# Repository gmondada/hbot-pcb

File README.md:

# HBOT - PCB

This is the KiCad projet for a 24-RC-servo controller. It has been designed to control the [HBOT Humanoid Robot](https://github.com/gmondada/hbot-main). It is based on a STM32F4 (Cortex M4) microcontroller and has a socket to hold a WEMOS D1 mini.

# The HBOT in action

See [Full Demo on YouTube](https://youtu.be/EHFqUxe0FO4).

# License

Copyright (c) 2019 Gabriele Mondada.
Licensed under the [Creative Commons CC-BY 4.0 License](https://creativecommons.org/licenses/by/4.0/legalcode).

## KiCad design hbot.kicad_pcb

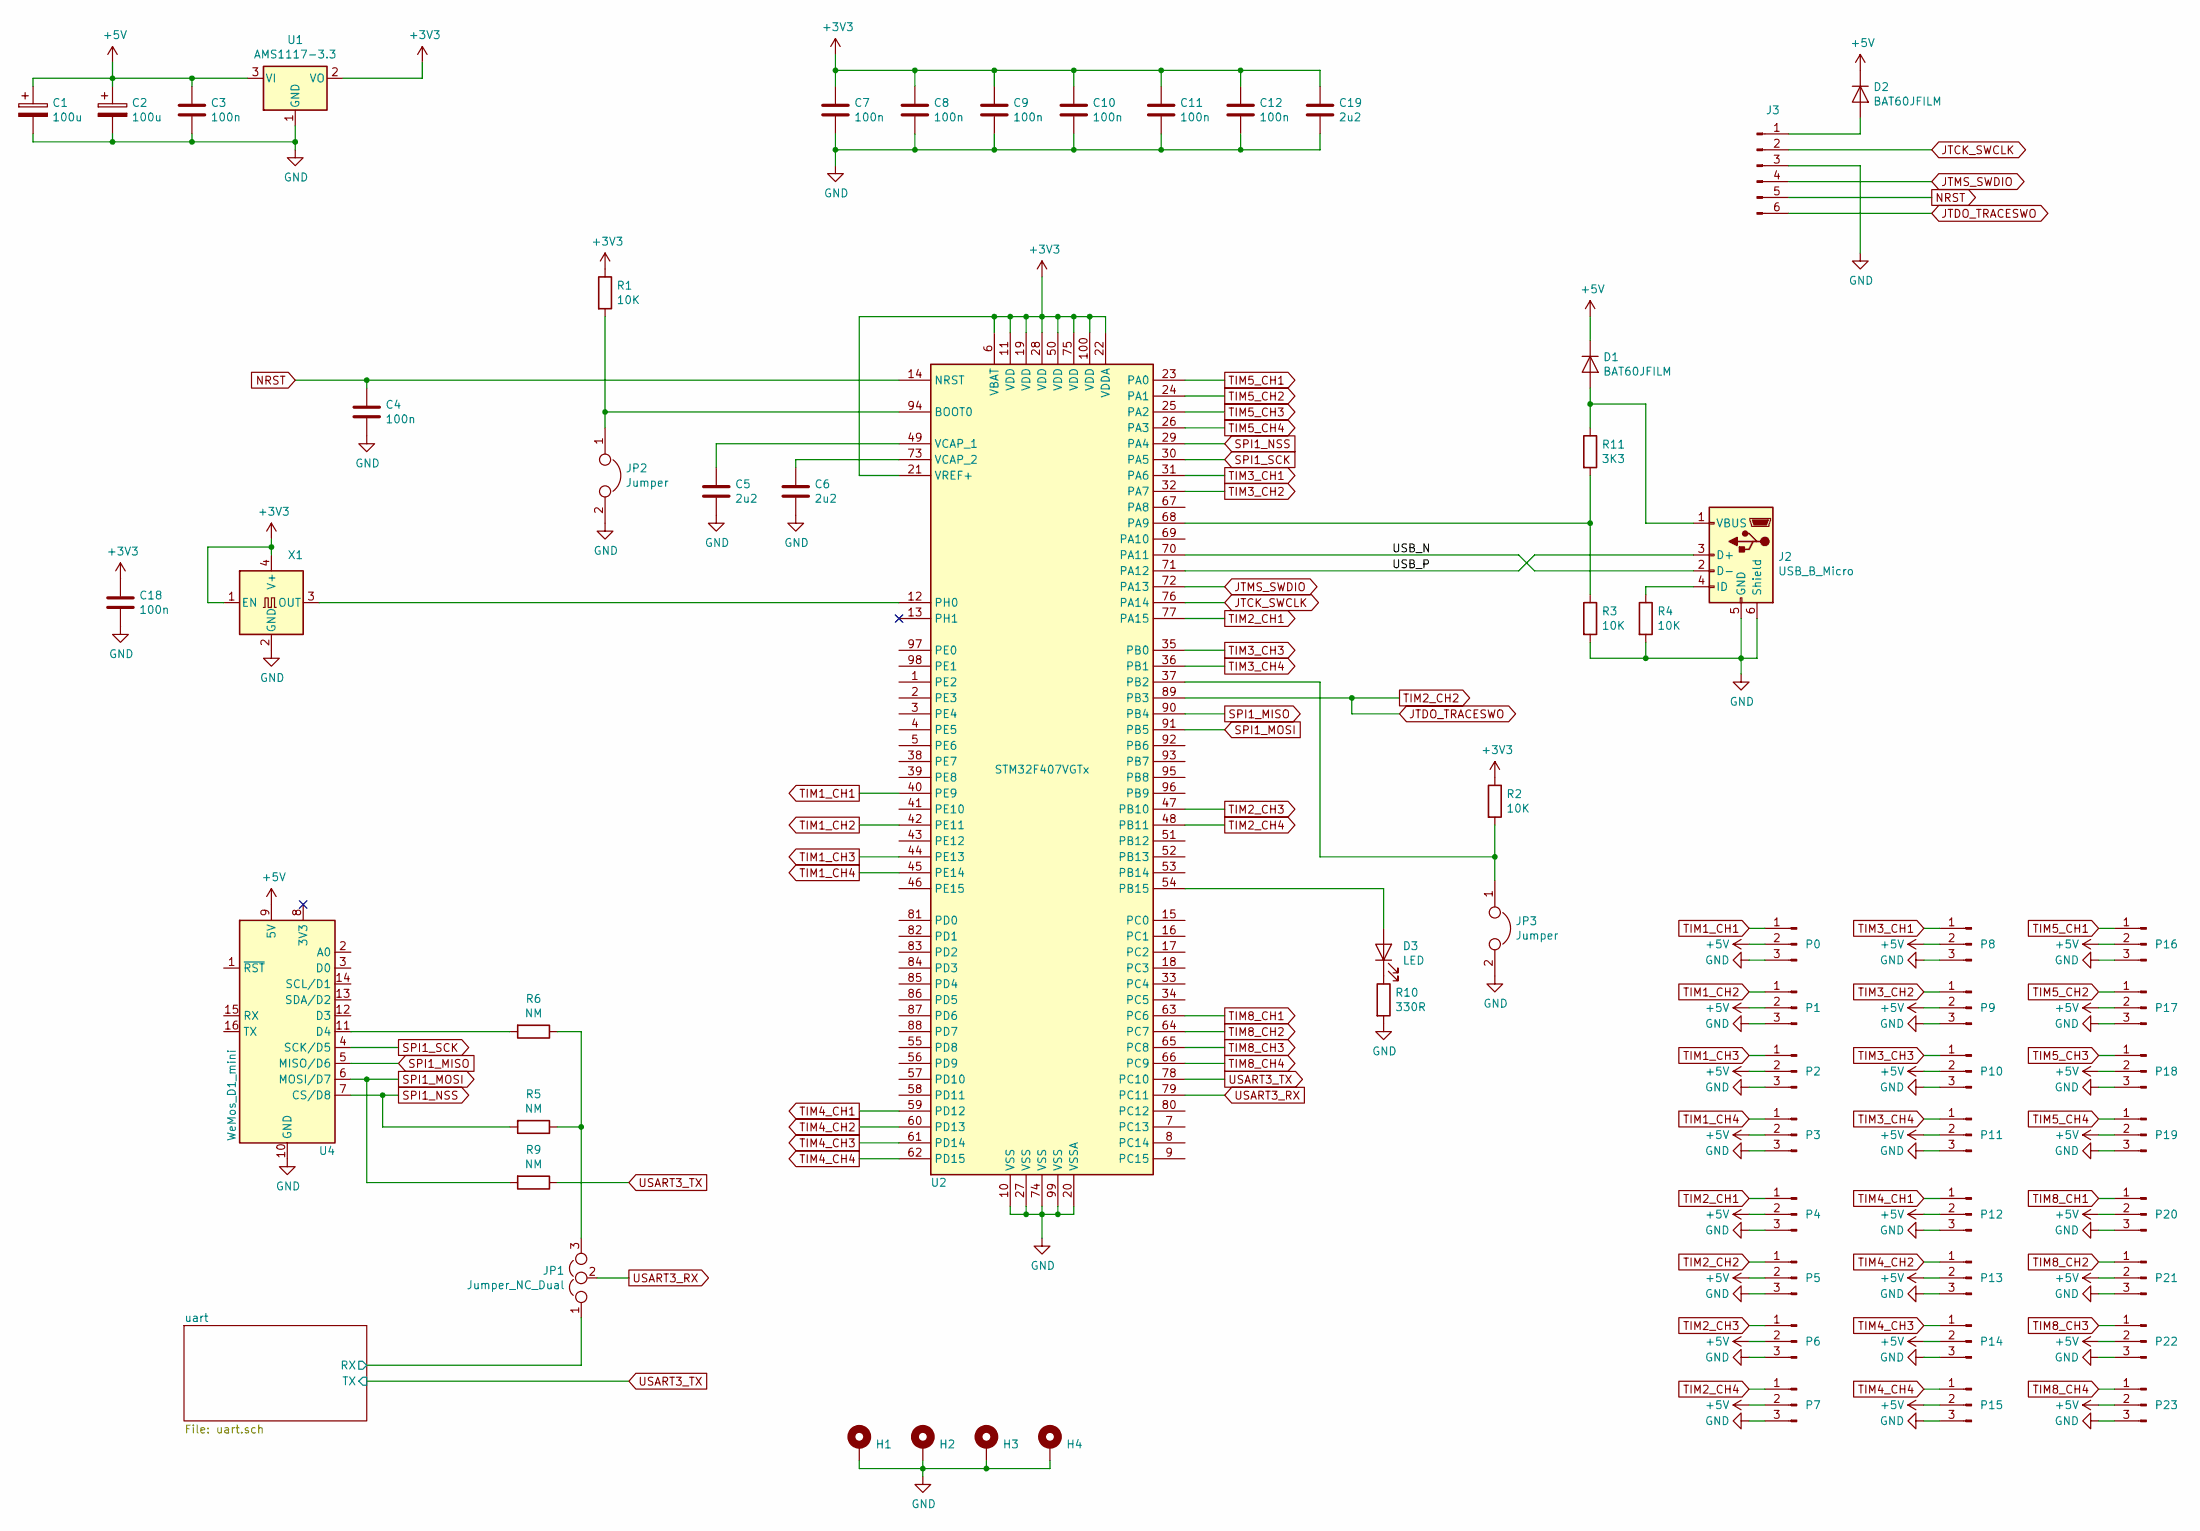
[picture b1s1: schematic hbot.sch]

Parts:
C1, C2: 100u; CP_Elec_6.3x7.7
C3, C4, C7, C8, C9, C10, C11, C12, C18: 100n; C_0603_1608Metric_Pad1.05x0.95mm_HandSolder
C5, C6, C19: 2u2; C_0603_1608Metric_Pad1.05x0.95mm_HandSolder
D1, D2: BAT60JFILM; D_SOD-323_HandSoldering
D3: LED; LED_0603_1608Metric_Pad1.05x0.95mm_HandSolder
H1, H2, H3, H4: MountingHole_Pad; MountingHole_2.2mm_M2_Pad_Via
J2: USB_B_Micro; USB_Micro-B_Wuerth_629105150521
J3: Conn_01x06_Male; PinHeader_1x06_P2.54mm_Vertical
JP1: Jumper_NC_Dual; PinHeader_1x03_P2.54mm_Vertical
JP2, JP3: Jumper; PinHeader_1x02_P2.54mm_Vertical
P0, P1, P2, P3, P4, P5, P6, P7, P8, P9, P10, P11, P12, P13, P14, P15, P16, P17, P18, P19, P20, P21, P22, P23: Conn_01x03_Male; PinHeader_1x03_P2.54mm_Vertical
R1, R2, R3, R4: 10K; R_0603_1608Metric_Pad1.05x0.95mm_HandSolder
R5, R6, R9: NM; R_0603_1608Metric_Pad1.05x0.95mm_HandSolder
R10: 330R; R_0603_1608Metric_Pad1.05x0.95mm_HandSolder
R11: 3K3; R_0603_1608Metric_Pad1.05x0.95mm_HandSolder
U1: AMS1117-3.3; SOT-223-3_TabPin2
U2: STM32F407VGTx; LQFP-100_14x14mm_P0.5mm
U4: WeMos_D1_mini; WEMOS_D1_mini_light
X1: XO53; Oscillator_SMD_EuroQuartz_XO53-4Pin_5.0x3.2mm

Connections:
+3V3: C7.1, C8.1, C9.1, C10.1, C11.1, C12.1, C18.1, C19.1, R1.1, R2.1, U1.2 (VO), U2.6 (VBAT), U2.11 (VDD), U2.19 (VDD), U2.21 (VREF+), U2.22 (VDDA), U2.28 (VDD), U2.50 (VDD), U2.75 (VDD), U2.100 (VDD), X1.1 (EN), X1.4 (V+); also elsewhere on the board
+5V: C1.1, C2.1, C3.1, D1.1 (K), D2.1 (K), P0.2, P1.2, P2.2, P3.2, P4.2, P5.2, P6.2, P7.2, P8.2, P9.2, P10.2, P11.2, P12.2, P13.2, P14.2, P15.2, P16.2, P17.2, P18.2, P19.2, P20.2, P21.2, P22.2, P23.2, U1.3 (VI), U4.9 (5V); also elsewhere on the board
/USB_N: J2.2 (D-), U2.70 (PA11)
/USB_P: J2.3 (D+), U2.71 (PA12)
/uart/RX: JP1.1; also elsewhere on the board
GND: C1.2, C2.2, C3.2, C4.2, C5.2, C6.2, C7.2, C8.2, C9.2, C10.2, C11.2, C12.2, C18.2, C19.2, H1.1, H2.1, H3.1, H4.1, J2.5 (GND), J2.6 (Shield), J3.3, JP2.2, JP3.2, P0.3, P1.3, P2.3, P3.3, P4.3, P5.3, P6.3, P7.3, P8.3, P9.3, P10.3, P11.3, P12.3, P13.3, P14.3, P15.3, P16.3, P17.3, P18.3, P19.3, P20.3, P21.3, P22.3, P23.3, R3.2, R4.2, R10.2, U1.1 (GND), U2.10 (VSS), U2.20 (VSSA), U2.27 (VSS), U2.74 (VSS), U2.99 (VSS), U4.10 (GND), X1.2 (GND); also elsewhere on the board
JTCK_SWCLK: J3.2, U2.76 (PA14)
JTDO_TRACESWO: J3.6, P5.1, U2.89 (PB3)
JTMS_SWDIO: J3.4, U2.72 (PA13)
NRST: C4.1, J3.5, U2.14 (NRST)
unnamed: C5.1, U2.49 (VCAP_1)
unnamed: C6.1, U2.73 (VCAP_2)
unnamed: D1.2 (A), J2.1 (VBUS), R11.1
unnamed: D2.2 (A), J3.1
unnamed: D3.1 (K), R10.1
unnamed: D3.2 (A), U2.54 (PB15)
unnamed: J2.4 (ID), R4.1
unnamed: JP1.3, R5.1, R6.1
unnamed: JP2.1, R1.2, U2.94 (BOOT0)
unnamed: JP3.1, R2.2, U2.37 (PB2)
unnamed: R6.2, U4.11 (D4)
unnamed: R3.1, R11.2, U2.68 (PA9)
unnamed: U2.12 (PH0), X1.3 (OUT)
SPI1_MISO: U2.90 (PB4), U4.5 (MISO/D6)
SPI1_MOSI: R9.2, U2.91 (PB5), U4.6 (MOSI/D7)
SPI1_NSS: R5.2, U2.29 (PA4), U4.7 (CS/D8)
SPI1_SCK: U2.30 (PA5), U4.4 (SCK/D5)
TIM1_CH1: P0.1, U2.40 (PE9)
TIM1_CH2: P1.1, U2.42 (PE11)
TIM1_CH3: P2.1, U2.44 (PE13)
TIM1_CH4: P3.1, U2.45 (PE14)
TIM2_CH1: P4.1, U2.77 (PA15)
TIM2_CH3: P6.1, U2.47 (PB10)
TIM2_CH4: P7.1, U2.48 (PB11)
TIM3_CH1: P8.1, U2.31 (PA6)
TIM3_CH2: P9.1, U2.32 (PA7)
TIM3_CH3: P10.1, U2.35 (PB0)
TIM3_CH4: P11.1, U2.36 (PB1)
TIM4_CH1: P12.1, U2.59 (PD12)
TIM4_CH2: P13.1, U2.60 (PD13)
TIM4_CH3: P14.1, U2.61 (PD14)
TIM4_CH4: P15.1, U2.62 (PD15)
TIM5_CH1: P16.1, U2.23 (PA0)
TIM5_CH2: P17.1, U2.24 (PA1)
TIM5_CH3: P18.1, U2.25 (PA2)
TIM5_CH4: P19.1, U2.26 (PA3)
TIM8_CH1: P20.1, U2.63 (PC6)
TIM8_CH2: P21.1, U2.64 (PC7)
TIM8_CH3: P22.1, U2.65 (PC8)
TIM8_CH4: P23.1, U2.66 (PC9)
USART3_RX: JP1.2, U2.79 (PC11)
USART3_TX: R9.1, U2.78 (PC10); also elsewhere on the board

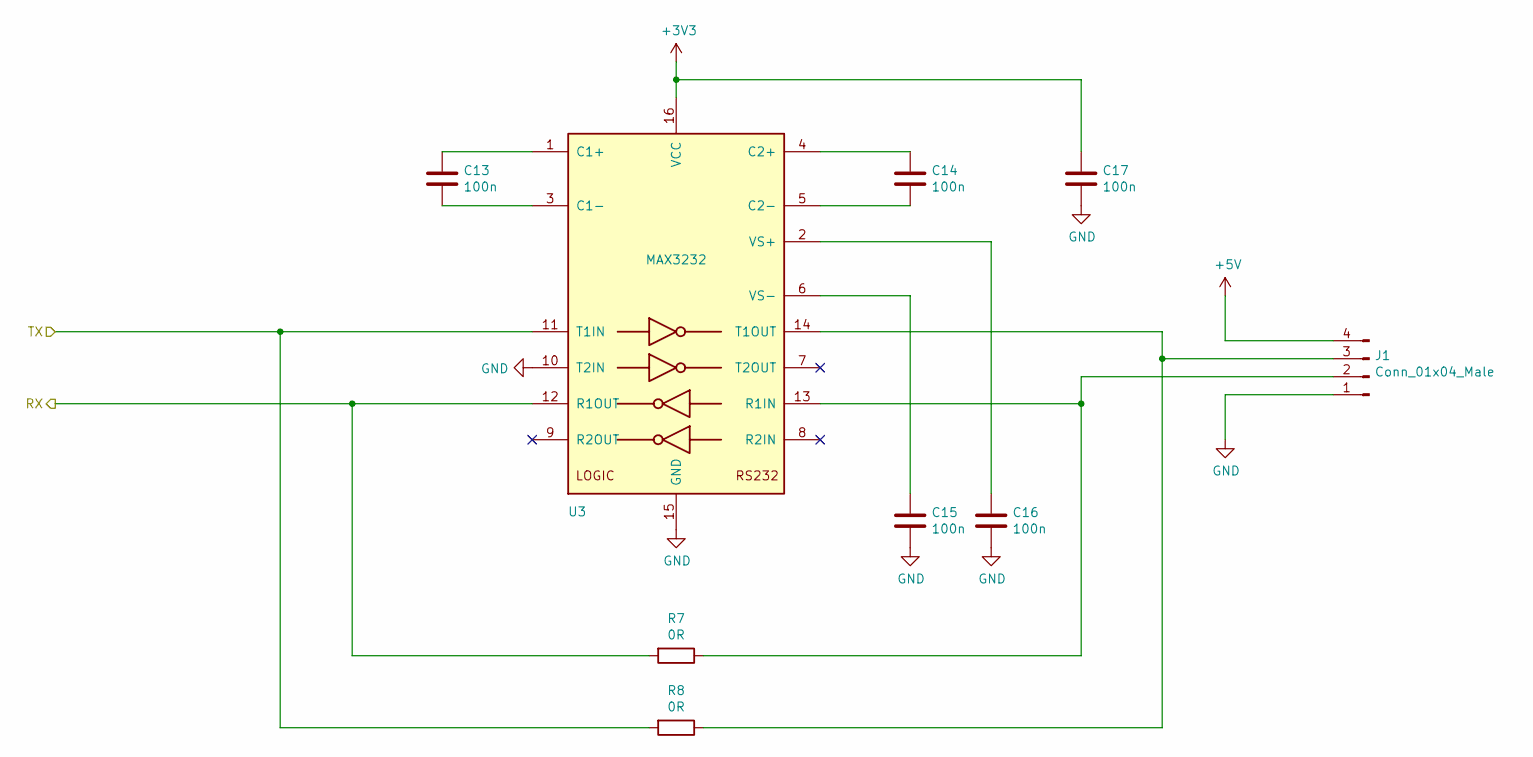
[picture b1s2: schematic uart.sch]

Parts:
C13, C14, C15, C16, C17: 100n; C_0603_1608Metric_Pad1.05x0.95mm_HandSolder
J1: Conn_01x04_Male; PinHeader_1x04_P2.54mm_Vertical
R7, R8: 0R; R_0603_1608Metric_Pad1.05x0.95mm_HandSolder
U3: MAX3232; TSSOP-16_4.4x5mm_P0.65mm

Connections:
+3V3: C17.1, U3.16 (VCC); also elsewhere on the board
+5V: J1.4; also elsewhere on the board
/uart/RX: R7.2, U3.12 (R1OUT); also elsewhere on the board
GND: C15.2, C16.2, C17.2, J1.1, U3.10 (T2IN), U3.15 (GND); also elsewhere on the board
unnamed: C13.1, U3.1 (C1+)
unnamed: C13.2, U3.3 (C1-)
unnamed: C14.1, U3.4 (C2+)
unnamed: C14.2, U3.5 (C2-)
unnamed: C15.1, U3.6 (VS-)
unnamed: C16.1, U3.2 (VS+)
unnamed: J1.2, R7.1, U3.13 (R1IN)
unnamed: J1.3, R8.1, U3.14 (T1OUT)
USART3_TX: R8.2, U3.11 (T1IN); also elsewhere on the board

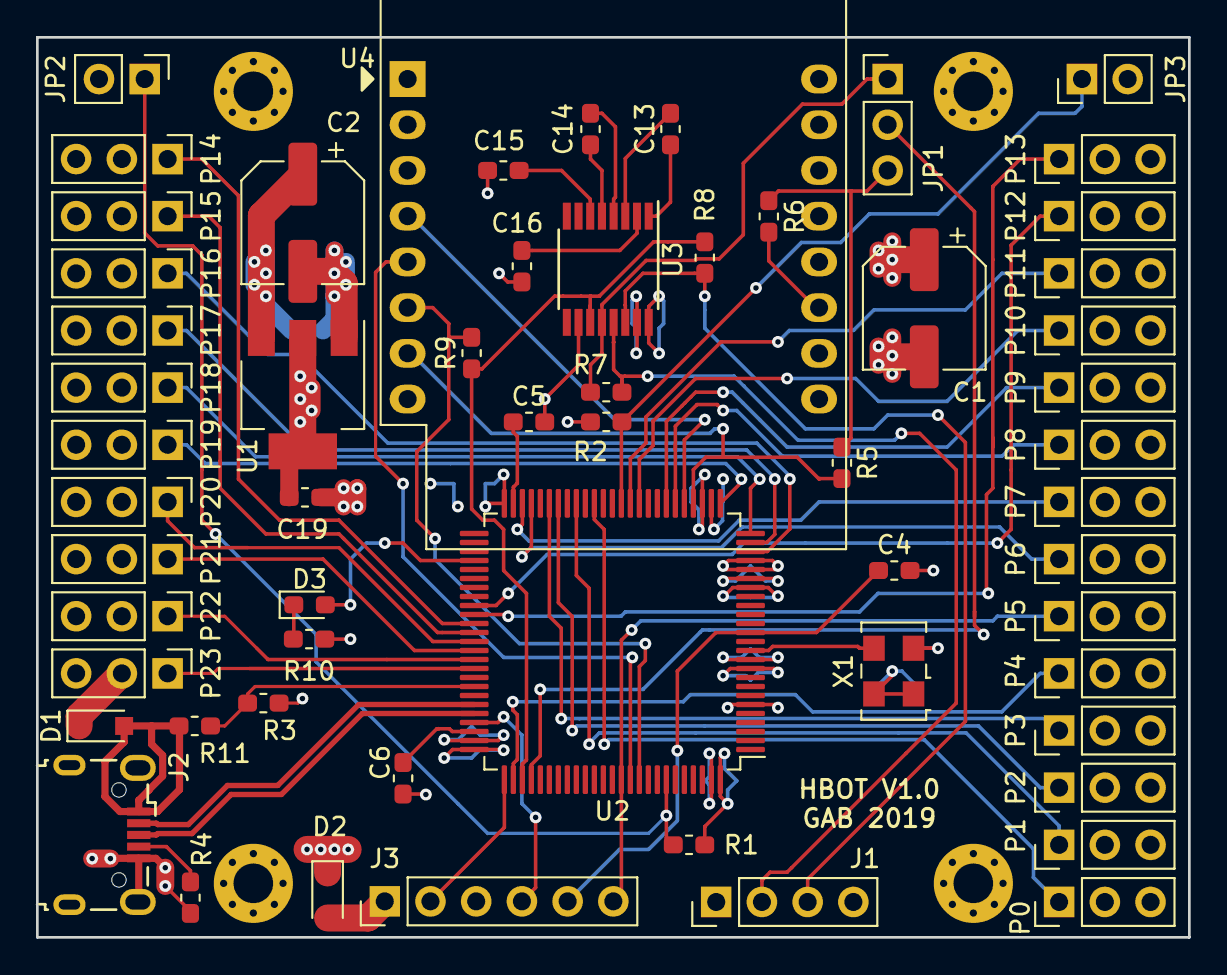
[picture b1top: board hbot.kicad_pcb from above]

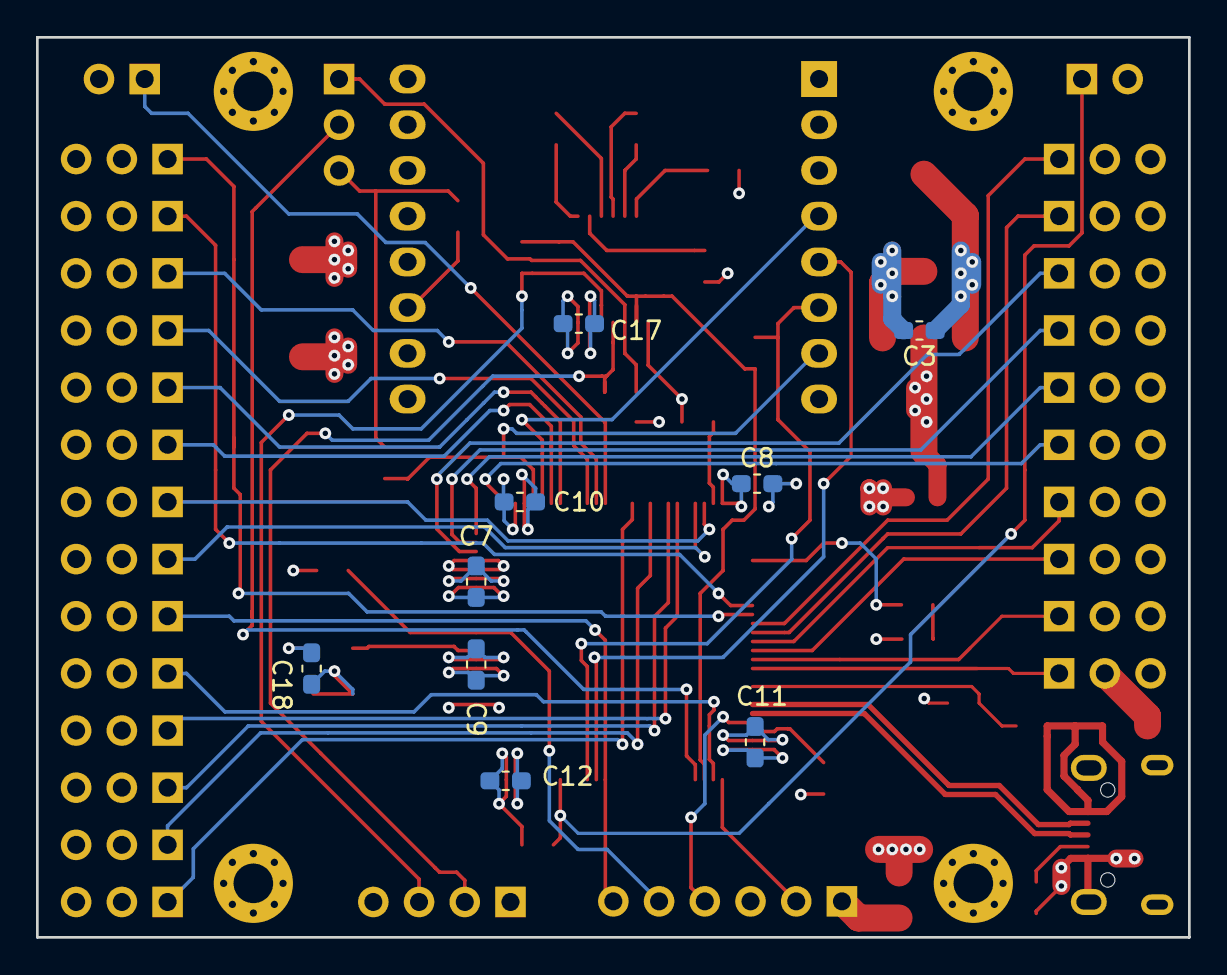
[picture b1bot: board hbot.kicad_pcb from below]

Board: 4 copper layers, 64.0 x 50.0 mm, 72 parts (9 on the bottom side), 60 nets.

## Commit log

2019-09-26 version 1.0
2019-09-26 add manufacturing files
2019-09-27 add README.md and related images
2019-09-27 add license
2020-05-28 add schematics in PDF format
2020-08-09 Add link to main project and to demo video
2020-08-09 improve README
